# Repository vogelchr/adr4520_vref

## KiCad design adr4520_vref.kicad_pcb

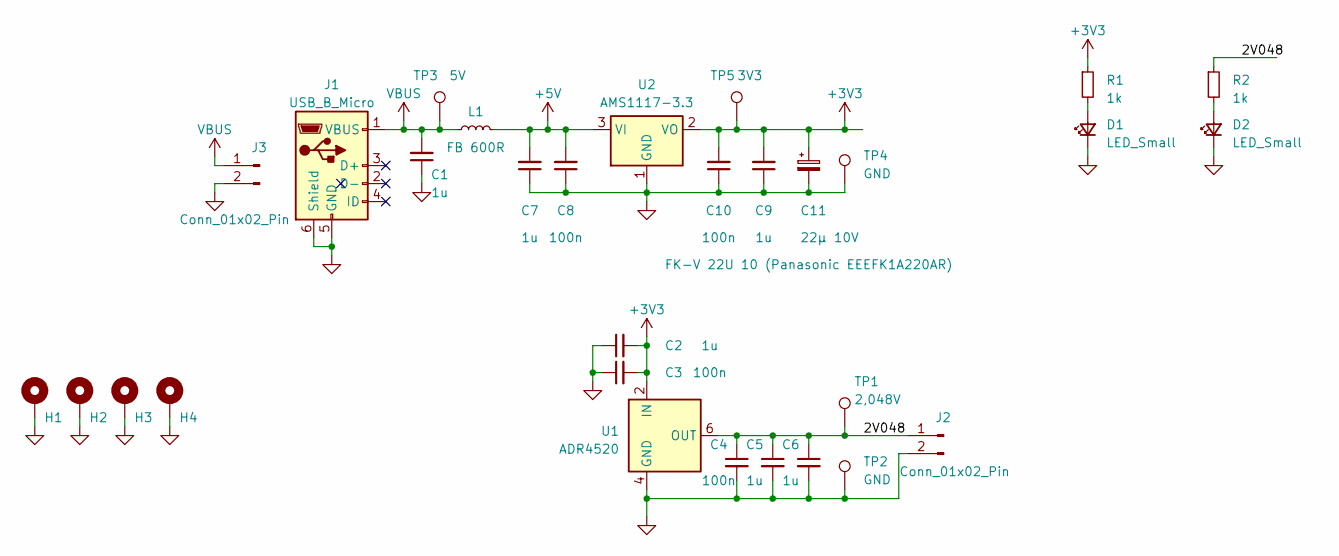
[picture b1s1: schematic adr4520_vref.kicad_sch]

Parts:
C1, C2, C5, C6, C7, C9: 1u; C_0603_1608Metric_Pad1.08x0.95mm_HandSolder
C3, C4, C8, C10: 100n; C_0603_1608Metric_Pad1.08x0.95mm_HandSolder
C11: 22µ 10V; CP_Elec_4x5.8
D1, D2: LED_Small; LED_0603_1608Metric_Pad1.05x0.95mm_HandSolder
H1, H2, H3, H4: MountingHole_Pad; MountingHole_3.2mm_M3_DIN965_Pad
J1: USB_B_Micro; USB_Micro-B_Wuerth_629105150521
J2, J3: Conn_01x02_Pin; PinHeader_1x02_P2.54mm_Horizontal
L1: FB 600R; L_0603_1608Metric_Pad1.05x0.95mm_HandSolder
R1, R2: 1k; R_0603_1608Metric_Pad0.98x0.95mm_HandSolder
TP1: 2,048V; TestPoint_Loop_D3.50mm_Drill1.4mm_Beaded
TP2, TP4: GND; TestPoint_Loop_D3.50mm_Drill1.4mm_Beaded
TP3: 5V; TestPoint_Loop_D3.50mm_Drill1.4mm_Beaded
TP5: 3V3; TestPoint_Loop_D3.50mm_Drill1.4mm_Beaded
U1: ADR4520; SOIC-8_3.9x4.9mm_P1.27mm
U2: AMS1117-3.3; SOT-223-3_TabPin2

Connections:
+3V3: C2.2, C3.2, C9.2, C10.2, C11.1, R1.1, TP5.1, U1.2 (IN), U2.2 (VO)
+5V: C7.2, C8.2, L1.2, U2.3 (VI)
/2V048: C4.1, C5.1, C6.1, J2.1, R2.1, TP1.1, U1.6 (OUT)
GND: C1.1, C2.1, C3.1, C4.2, C5.2, C6.2, C7.1, C8.1, C9.1, C10.1, C11.2, D1.1 (K), D2.1 (K), H1.1, H2.1, H3.1, H4.1, J1.5 (GND), J1.6 (Shield), J2.2, J3.2, TP2.1, TP4.1, U1.4 (GND), U2.1 (GND)
unnamed: D1.2 (A), R1.2
unnamed: D2.2 (A), R2.2
VBUS: C1.2, J1.1 (VBUS), J3.1, L1.1, TP3.1

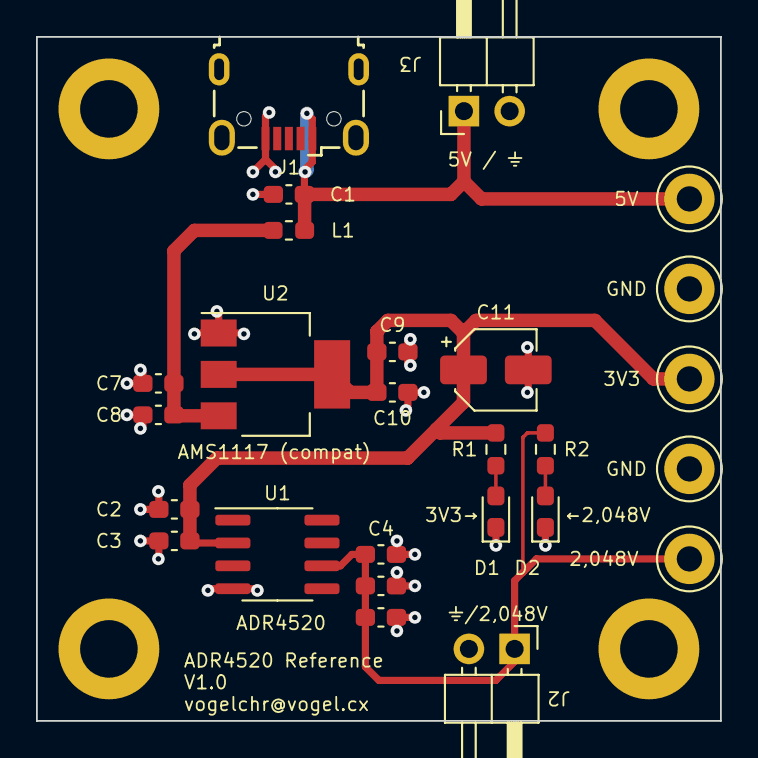
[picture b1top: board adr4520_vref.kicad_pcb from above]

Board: 2 copper layers, 38.0 x 38.0 mm, 30 parts (0 on the bottom side), 7 nets.

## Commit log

2023-05-14 Initially empty repository.
2023-05-14 v1.0
